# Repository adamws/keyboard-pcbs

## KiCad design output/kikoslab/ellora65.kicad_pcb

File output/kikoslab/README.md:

## kikoslab/ellora65

[layout](ellora65-kle.json) - [PCB](ellora65.kicad_pcb)

{:loading="lazy"}

[Open in keyboard-layout-editor](http://www.keyboard-layout-editor.com/##@@_x:1.25&c=#aaaaaa;&=0,0;&@_x:2.5&y:-0.75&c=#777777;&=1,0&_c=#cccccc;&=0,1&=1,1&=0,2&=1,2&=0,3&=1,3&=0,4&=1,4&=0,5&=1,5&=0,6&=1,6&_c=#aaaaaa&w:2;&=0,7%0A%0A%0A0,0;&@_x:1.25;&=2,0&_x:0.25&w:1.5;&=3,0&_c=#cccccc;&=2,1&=3,1&=2,2&=3,2&=2,3&=3,3&=2,4&=3,4&=2,5&=3,5&=2,6&=3,6&_c=#aaaaaa&w:1.5;&=2,7%0A%0A%0A1,0;&@_x:1.25;&=4,0&_x:0.25&w:1.75;&=5,0&_c=#cccccc;&=4,1&=5,1&=4,2&=5,2&=4,3&=5,3&=4,4&=5,4&=4,5&=5,5&=4,6&_c=#777777&w:2.25;&=4,7%0A%0A%0A1,0&_c=#aaaaaa;&=5,7;&@_x:1.25;&=6,0&_x:0.25&w:2.25;&=7,0%0A%0A%0A2,0&_c=#cccccc;&=7,1&=6,2&=7,2&=6,3&=7,3&=6,4&=7,4&=6,5&=7,5&=6,6&_c=#aaaaaa&w:1.75;&=7,6&_c=#777777;&=6,7&_c=#aaaaaa;&=7,7;&@_x:1.25;&=8,0&_x:0.25&w:1.25;&=9,0%0A%0A%0A3,0&_w:1.25;&=8,1%0A%0A%0A3,0&_w:1.25;&=9,1%0A%0A%0A3,0&_w:6.25;&=8,3%0A%0A%0A3,0&=9,5%0A%0A%0A3,0&_w:1.5;&=8,6%0A%0A%0A3,0&_x:0.5&c=#777777;&=9,6&=8,7&=9,7;&@_x:17.75&y:-5.0&c=#aaaaaa;&=0,7%0A%0A%0A0,1&=1,7%0A%0A%0A0,1;&@_x:19.75&y:0.5&c=#777777&w:1.25&h:2&w2:1.5&h2:1&x2:-0.25;&=4,7%0A%0A%0A1,1;&@_x:18.75&c=#aaaaaa;&=5,6%0A%0A%0A1,1;&@_x:2.5&y:1.5&w:1.25;&=9,0%0A%0A%0A3,1&_w:1.25;&=8,1%0A%0A%0A3,1&_w:1.25;&=9,1%0A%0A%0A3,1&_w:2.75;&=8,2%0A%0A%0A3,1&_w:1.25;&=8,3%0A%0A%0A3,1&_w:2.25;&=8,4%0A%0A%0A3,1&=9,5%0A%0A%0A3,1&_w:1.5;&=8,6%0A%0A%0A3,1;&@_w:1.25;&=7,0%0A%0A%0A2,1&=6,1%0A%0A%0A2,1&_x:0.25&w:1.5;&=9,0%0A%0A%0A3,2&=8,1%0A%0A%0A3,2&_w:1.5;&=9,1%0A%0A%0A3,2&_w:7;&=8,3%0A%0A%0A3,2&_w:1.5;&=8,6%0A%0A%0A3,2)

{:loading="lazy"}

## kikoslab/kl90

[layout](kl90-kle.json) - [PCB](kl90.kicad_pcb)

{:loading="lazy"}

[Open in keyboard-layout-editor](http://www.keyboard-layout-editor.com/##@@_c=#aaaaaa;&=0,0&_x:0.5&c=#777777;&=0,1&_x:0.25&c=#aaaaaa;&=0,2&=0,3&=0,4&=0,5&_x:0.25;&=0,6&=0,7&=0,8&=0,9&_x:0.25;&=0,10&=0,11&=0,12&=0,13&_x:0.25;&=0,14%0A%0A%0A0,0&_x:0.5;&=0,15%0A%0A%0A0,0;&@_y:0.5;&=1,0&_x:0.5;&=1,1&_c=#cccccc;&=1,2&=1,3&=1,4&=1,5&=1,6&=1,7&=1,8&=1,9&=1,10&=1,11&=1,12&=1,13&_c=#aaaaaa&w:2;&=1,14&_x:0.5;&=1,15;&@=2,0&_x:0.5&w:1.5;&=2,1&_c=#cccccc;&=2,2&=2,3&=2,4&=2,5&=2,6&=2,7&=2,8&=2,9&=2,10&=2,11&=2,12&=2,13&_c=#aaaaaa&w:1.5;&=2,14%0A%0A%0A1,0&_x:0.5;&=2,15;&@=3,0&_x:0.5&w:1.75;&=3,1&_c=#cccccc;&=3,2&=3,3&=3,4&=3,5&=3,6&=3,7&=3,8&=3,9&=3,10&=3,11&=3,12&_c=#777777&w:2.25;&=3,14%0A%0A%0A1,0&_x:0.5&c=#aaaaaa;&=3,15;&@=4,0&_x:0.5&w:2.25;&=4,1%0A%0A%0A2,0&_c=#cccccc;&=4,2&=4,3&=4,4&=4,5&=4,6&=4,7&=4,8&=4,9&=4,10&=4,11&_c=#aaaaaa&w:1.75;&=4,13&_x:1.5;&=4,15;&@_x:15.75&y:-0.75&c=#777777;&=4,14;&@_y:-0.25&c=#aaaaaa;&=5,0&_x:0.5&w:1.25;&=5,1&_w:1.25;&=5,2&_w:1.25;&=5,3&_w:6.25;&=5,6%0A%0A%0A3,0&_w:1.5;&=5,10%0A%0A%0A4,0&_w:1.5;&=5,11%0A%0A%0A4,0;&@_x:14.75&y:-0.75&c=#777777;&=5,13&=5,14&=5,15;&@_x:18.5&y:-6.75&c=#cccccc&w:2&d:true;&=%0A%0A%0A0,1;&@_x:19.5&y:1.5&c=#aaaaaa&w:1.25&h:2&w2:1.5&h2:1&x2:-0.25;&=3,14%0A%0A%0A1,1;&@_x:18.5;&=3,13%0A%0A%0A1,1;&@_x:1.5&y:2.0&w:1.25;&=4,1%0A%0A%0A2,1&=4,12%0A%0A%0A2,1&_x:1.5&w:2.25;&=5,4%0A%0A%0A3,1&_w:1.25;&=5,6%0A%0A%0A3,1&_w:2.75;&=5,8%0A%0A%0A3,1&=5,10%0A%0A%0A4,1&=5,11%0A%0A%0A4,1&=5,12%0A%0A%0A4,1;&@_x:5.25&w:6.25;&=5,5%0A%0A%0A3,2;&@_x:5.25&w:2.25;&=5,4%0A%0A%0A3,3&_w:1.25;&=5,5%0A%0A%0A3,3&_w:2.75;&=5,8%0A%0A%0A3,3)

{:loading="lazy"}

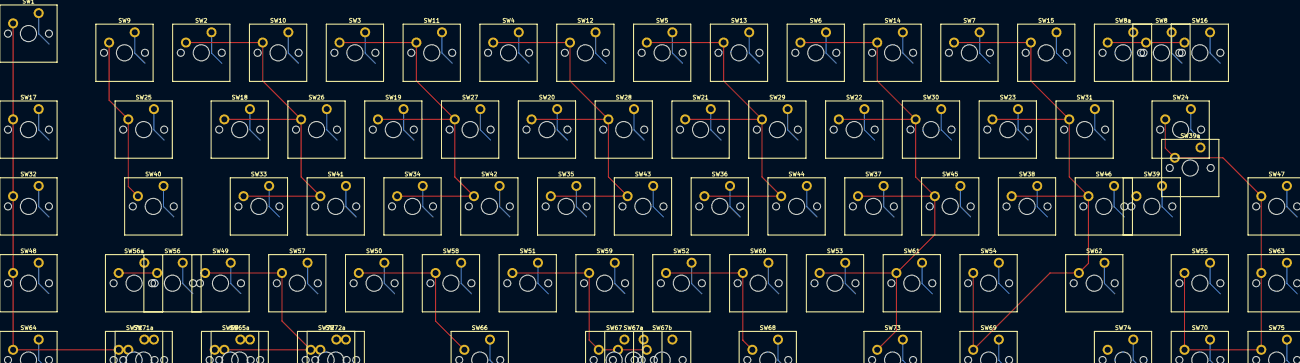
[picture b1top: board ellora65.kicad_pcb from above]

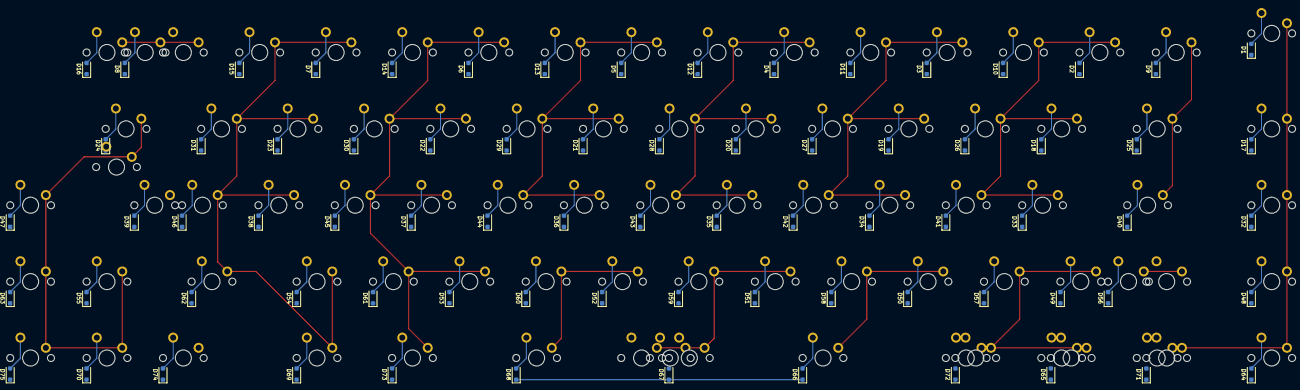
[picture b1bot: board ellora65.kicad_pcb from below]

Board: 2 copper layers, 158 parts (75 on the bottom side), 93 nets.

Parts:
D1, D2, D3, D4, D5, D6, D7, D8, D9, D10, D11, D12, D13, D14, D15, D16, D17, D18, D19, D20, D21, D22, D23, D24, D25, D26, D27, D28, D29, D30, D31, D32, D33, D34, D35, D36, D37, D38, D39, D40, D41, D42, D43, D44, D45, D46, D47, D48, D49, D50, D51, D52, D53, D54, D55, D56, D57, D58, D59, D60, D61, D62, D63, D64, D65, D66, D67, D68, D69, D70, D71, D72, D73, D74, D75: D_SOD-123F
SW1, SW2, SW3, SW4, SW5, SW6, SW7, SW8, SW8a, SW9, SW10, SW11, SW12, SW13, SW14, SW15, SW16, SW17, SW18, SW19, SW20, SW21, SW22, SW23, SW24, SW25, SW26, SW27, SW28, SW29, SW30, SW31, SW32, SW33, SW34, SW35, SW36, SW37, SW38, SW39, SW39a, SW40, SW41, SW42, SW43, SW44, SW45, SW46, SW47, SW48, SW49, SW50, SW51, SW52, SW53, SW54, SW55, SW56, SW56a, SW57, SW58, SW59, SW60, SW61, SW62, SW63, SW64, SW65, SW65a, SW66, SW67, SW67a, SW67b, SW68, SW69, SW70, SW71, SW71a, SW72, SW72a, SW73, SW74, SW75: SW_Cherry_MX_PCB_1.00u

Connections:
COL0: SW1.1, SW9.1, SW17.1, SW25.1, SW32.1, SW40.1, SW48.1, SW56.1, SW56a.1, SW64.1, SW71.1, SW71a.1
COL1: SW2.1, SW10.1, SW18.1, SW26.1, SW33.1, SW41.1, SW49.1, SW57.1, SW65.1, SW65a.1, SW72.1, SW72a.1
COL2: SW3.1, SW11.1, SW19.1, SW27.1, SW34.1, SW42.1, SW50.1, SW58.1, SW66.1
COL3: SW4.1, SW12.1, SW20.1, SW28.1, SW35.1, SW43.1, SW51.1, SW59.1, SW67.1, SW67a.1, SW67b.1
COL4: SW5.1, SW13.1, SW21.1, SW29.1, SW36.1, SW44.1, SW52.1, SW60.1, SW68.1
COL5: SW6.1, SW14.1, SW22.1, SW30.1, SW37.1, SW45.1, SW53.1, SW61.1, SW73.1
COL6: SW7.1, SW15.1, SW23.1, SW31.1, SW38.1, SW46.1, SW54.1, SW62.1, SW69.1, SW74.1
COL7: SW8.1, SW8a.1, SW16.1, SW24.1, SW39.1, SW39a.1, SW47.1, SW55.1, SW63.1, SW70.1, SW75.1
unnamed: D1.2, SW1.2
unnamed: D2.2, SW2.2
unnamed: D3.2, SW3.2
unnamed: D4.2, SW4.2
unnamed: D5.2, SW5.2
unnamed: D6.2, SW6.2
unnamed: D7.2, SW7.2
unnamed: D8.2, SW8.2, SW8a.2
unnamed: D9.2, SW9.2
unnamed: D10.2, SW10.2
unnamed: D11.2, SW11.2
unnamed: D12.2, SW12.2
unnamed: D13.2, SW13.2
unnamed: D14.2, SW14.2
unnamed: D15.2, SW15.2
unnamed: D16.2, SW16.2
unnamed: D17.2, SW17.2
unnamed: D18.2, SW18.2
unnamed: D19.2, SW19.2
unnamed: D20.2, SW20.2
unnamed: D21.2, SW21.2
unnamed: D22.2, SW22.2
unnamed: D23.2, SW23.2
unnamed: D24.2, SW24.2
unnamed: D25.2, SW25.2
unnamed: D26.2, SW26.2
unnamed: D27.2, SW27.2
unnamed: D28.2, SW28.2
unnamed: D29.2, SW29.2
unnamed: D30.2, SW30.2
unnamed: D31.2, SW31.2
unnamed: D32.2, SW32.2
unnamed: D33.2, SW33.2
unnamed: D34.2, SW34.2
unnamed: D35.2, SW35.2
unnamed: D36.2, SW36.2
unnamed: D37.2, SW37.2
unnamed: D38.2, SW38.2
unnamed: D39.2, SW39.2, SW39a.2
unnamed: D40.2, SW40.2
unnamed: D41.2, SW41.2
unnamed: D42.2, SW42.2
unnamed: D43.2, SW43.2
unnamed: D44.2, SW44.2
unnamed: D45.2, SW45.2
unnamed: D46.2, SW46.2
unnamed: D47.2, SW47.2
unnamed: D48.2, SW48.2
unnamed: D49.2, SW49.2
unnamed: D50.2, SW50.2
unnamed: D51.2, SW51.2
unnamed: D52.2, SW52.2
unnamed: D53.2, SW53.2
unnamed: D54.2, SW54.2
unnamed: D55.2, SW55.2
unnamed: D56.2, SW56.2, SW56a.2
unnamed: D57.2, SW57.2
unnamed: D58.2, SW58.2
unnamed: D59.2, SW59.2
unnamed: D60.2, SW60.2
unnamed: D61.2, SW61.2
unnamed: D62.2, SW62.2
unnamed: D63.2, SW63.2
unnamed: D64.2, SW64.2
unnamed: D65.2, SW65.2, SW65a.2
unnamed: D66.2, SW66.2
unnamed: D67.2, SW67.2, SW67a.2, SW67b.2
unnamed: D68.2, SW68.2
unnamed: D69.2, SW69.2
unnamed: D70.2, SW70.2
unnamed: D71.2, SW71.2, SW71a.2
unnamed: D72.2, SW72.2, SW72a.2
unnamed: D73.2, SW73.2
unnamed: D74.2, SW74.2
unnamed: D75.2, SW75.2
ROW0: D1.1, D2.1, D3.1, D4.1, D5.1, D6.1, D7.1, D8.1
ROW1: D9.1, D10.1, D11.1, D12.1, D13.1, D14.1, D15.1, D16.1
ROW2: D17.1, D18.1, D19.1, D20.1, D21.1, D22.1, D23.1, D24.1
ROW3: D25.1, D26.1, D27.1, D28.1, D29.1, D30.1, D31.1
ROW4: D32.1, D33.1, D34.1, D35.1, D36.1, D37.1, D38.1, D39.1
ROW5: D40.1, D41.1, D42.1, D43.1, D44.1, D45.1, D46.1, D47.1
ROW6: D48.1, D49.1, D50.1, D51.1, D52.1, D53.1, D54.1, D55.1
ROW7: D56.1, D57.1, D58.1, D59.1, D60.1, D61.1, D62.1, D63.1
ROW8: D64.1, D65.1, D66.1, D67.1, D68.1, D69.1, D70.1
ROW9: D71.1, D72.1, D73.1, D74.1, D75.1
